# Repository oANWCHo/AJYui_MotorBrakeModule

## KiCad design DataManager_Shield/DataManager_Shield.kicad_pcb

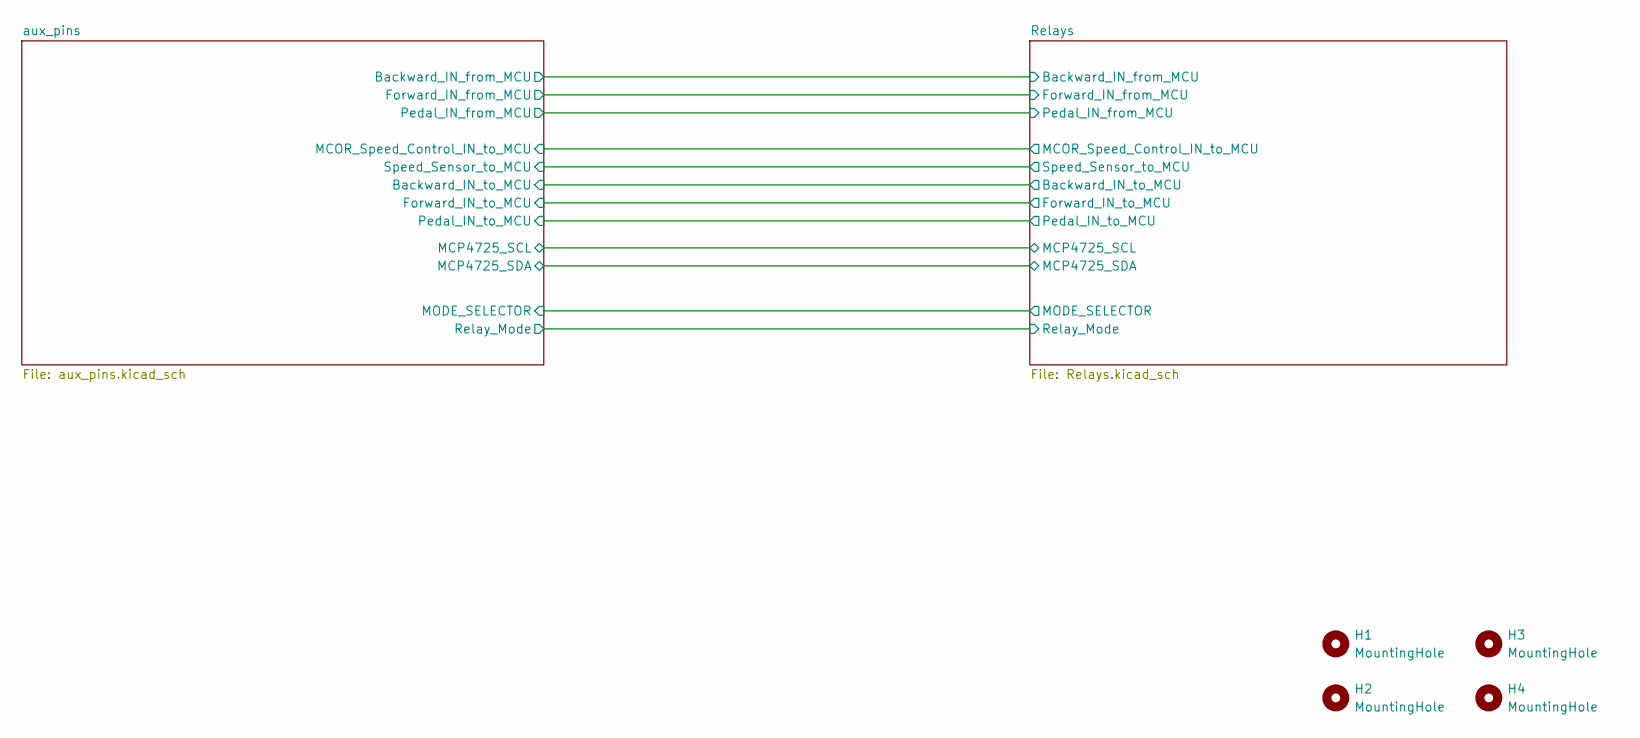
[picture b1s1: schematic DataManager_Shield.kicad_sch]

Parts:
H1, H2, H3, H4: MountingHole; MountingHole_3.2mm_M3_DIN965_Pad

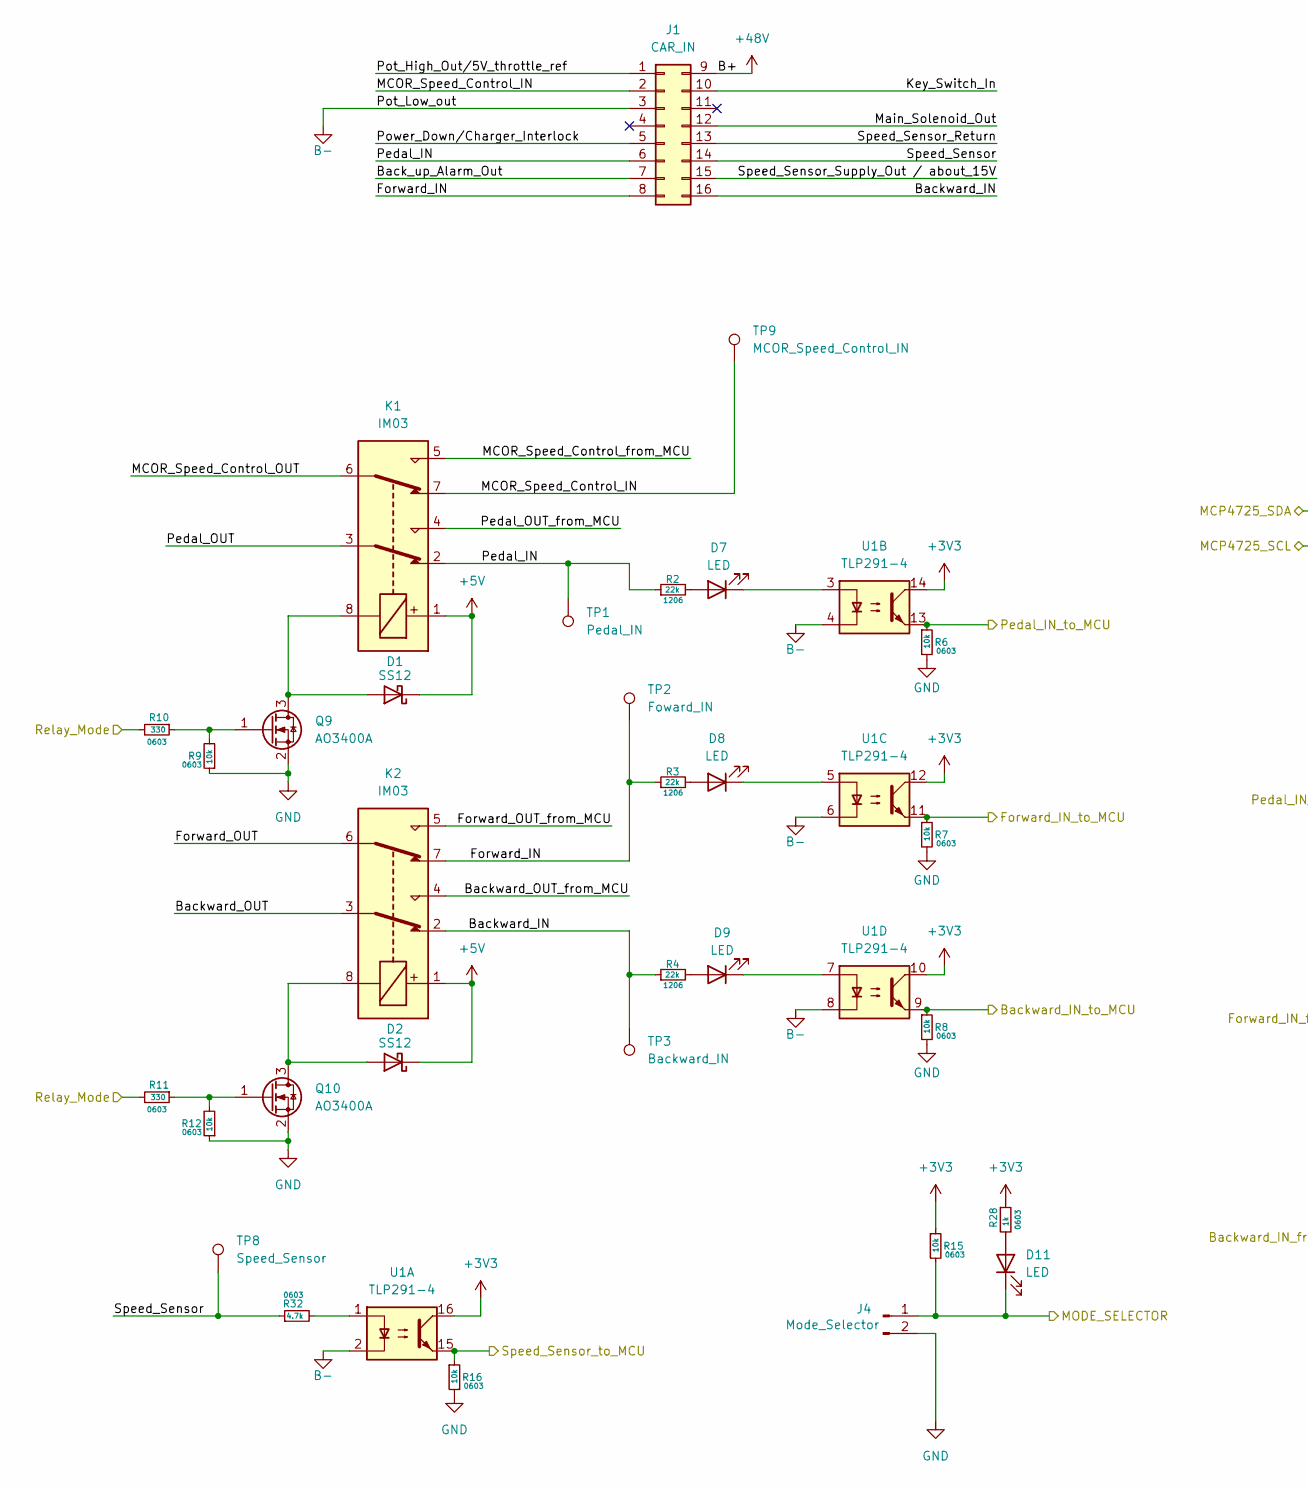
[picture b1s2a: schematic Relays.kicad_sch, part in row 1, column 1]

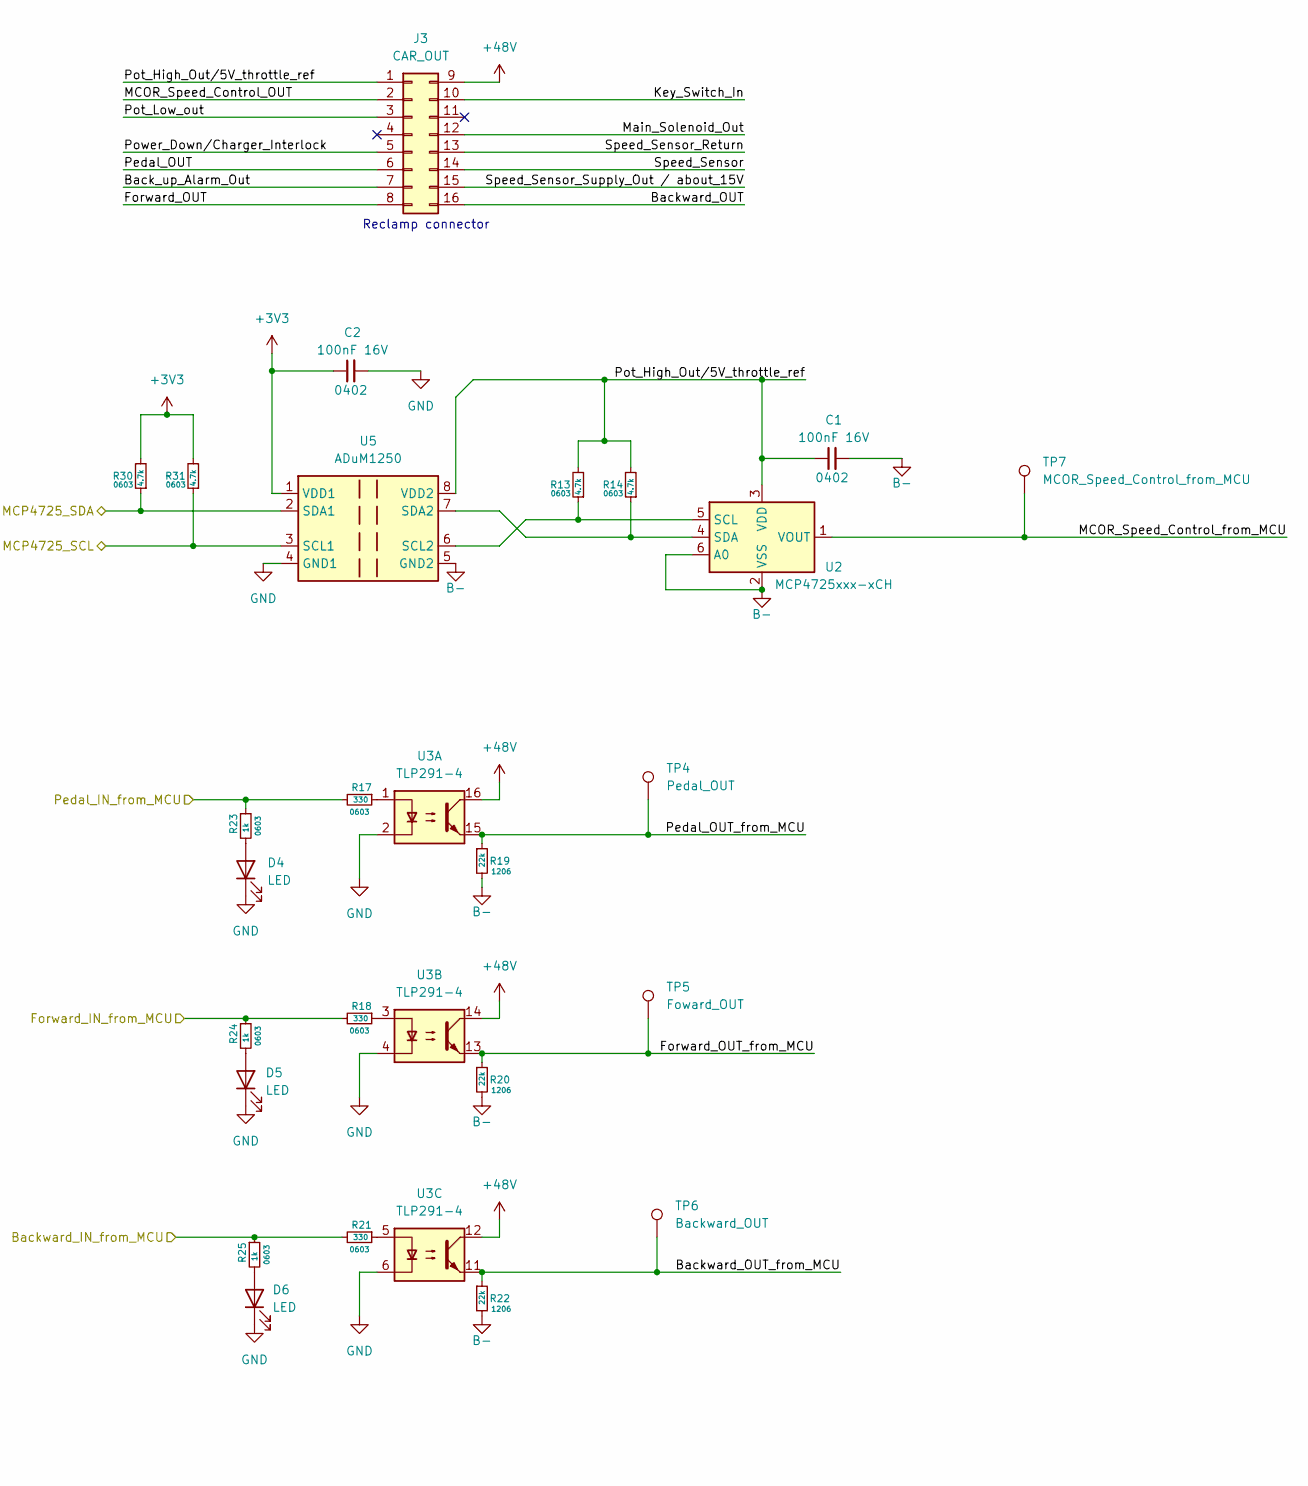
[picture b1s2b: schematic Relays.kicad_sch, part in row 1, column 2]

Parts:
C1, C2: 100nF 16V; C_0402_1005Metric; JLCPCB Part # C1525
D1, D2: SS12; D_SMA; JLCPCB Part # C18199177
D4, D5, D6, D7, D8, D9, D11: LED; LED_0603_1608Metric; JLCPCB Part # C2287
J1: CAR_IN; Molex_Mini-Fit_Jr_5569-16A2_2x08_P4.20mm_Horizontal; JLCPCB Part # C485577
J3: CAR_OUT; Molex_Mini-Fit_Jr_5569-16A2_2x08_P4.20mm_Horizontal; JLCPCB Part # C485577
J4: Mode_Selector; JST_XH_S2B-XH-A_1x02_P2.50mm_Horizontal; JLCPCB Part # C163035
K1, K2: IM03; Relay_2P2T_10x6mm_TE_IMxxG; JLCPCB Part # C2153100
Q9, Q10: AO3400A; SOT-23; JLCPCB Part # C20917
R2, R3, R4, R19, R20, R22: 22k; R_1206_3216Metric; JLCPCB Part # C25654
R6, R7, R8, R9, R12, R15, R16: 10k; R_0603_1608Metric; JLCPCB Part # C130232
R10, R11, R17, R18, R21: 330; R_0603_1608Metric; JLCPCB Part # C23138
R13, R14, R30, R31, R32: 4.7k; R_0603_1608Metric; JLCPCB Part # C23162
R23, R24, R25, R28: 1k; R_0603_1608Metric; JLCPCB Part # C21190
TP1: Pedal_IN; TestPoint_Pad_1.0x1.0mm
TP2: Foward_IN; TestPoint_Pad_1.0x1.0mm
TP3: Backward_IN; TestPoint_Pad_1.0x1.0mm
TP4: Pedal_OUT; TestPoint_Pad_1.0x1.0mm
TP5: Foward_OUT; TestPoint_Pad_1.0x1.0mm
TP6: Backward_OUT; TestPoint_Pad_1.0x1.0mm
TP7: MCOR_Speed_Control_from_MCU; TestPoint_Pad_1.0x1.0mm
TP8: Speed_Sensor; TestPoint_Pad_1.0x1.0mm
TP9: MCOR_Speed_Control_IN; TestPoint_Pad_1.0x1.0mm
U1, U3: TLP291-4; SOP-16_4.4x10.4mm_P1.27mm; JLCPCB Part # C60900
U2: MCP4725xxx-xCH; SOT-23-6; JLCPCB Part # C144198
U5: ADuM1250; SOIC-8_3.9x4.9mm_P1.27mm; JLCPCB Part # C13839

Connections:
+3V3: C2.1, R15.1, R28.1, R30.2, R31.2, U1.10, U1.12, U1.14, U1.16, U5.1 (VDD1); also elsewhere on the board
+5V: D1.1 (K), D2.1 (K), K1.1, K2.1; also elsewhere on the board
+48V: J1.9, J3.9, U3.12, U3.14, U3.16
/Relays/ Speed_Sensor_Supply_Out / about_15V: J1.15, J3.15
/Relays/Back_up_Alarm_Out: J1.7, J3.7
/Relays/Backward_IN: J1.16, K2.2, R4.1, TP3.1 (1_1)
/Relays/Backward_OUT: J3.16, K2.3
/Relays/Backward_OUT_from_MCU: K2.4, R22.1, TP6.1 (1_1), U3.11
/Relays/Forward_IN: J1.8, K2.7, R3.1, TP2.1 (1_1)
/Relays/Forward_OUT: J3.8, K2.6
/Relays/Forward_OUT_from_MCU: K2.5, R20.1, TP5.1 (1_1), U3.13
/Relays/Key_Switch_In: J1.10, J3.10
/Relays/MCOR_Speed_Control_IN: J1.2, K1.7, TP9.1 (1_1)
/Relays/MCOR_Speed_Control_OUT: J3.2, K1.6
/Relays/MCOR_Speed_Control_from_MCU: K1.5, TP7.1 (1_1), U2.1 (VOUT)
/Relays/Main_Solenoid_Out: J1.12, J3.12
/Relays/Pedal_IN: J1.6, K1.2, R2.1, TP1.1 (1_1)
/Relays/Pedal_OUT: J3.6, K1.3
/Relays/Pedal_OUT_from_MCU: K1.4, R19.1, TP4.1 (1_1), U3.15
/Relays/Pot_High_Out/5V_throttle_ref: C1.1, J1.1, J3.1, R13.2, R14.2, U2.3 (VDD), U5.8 (VDD2)
/Relays/Power_Down/Charger_Interlock: J1.5, J3.5
/Relays/Speed_Sensor: J1.14, J3.14, R32.1, TP8.1 (1_1)
/Relays/Speed_Sensor_Return: J1.13, J3.13
/aux_pins/PA8: R30.1, U5.2 (SDA1); also elsewhere on the board
/aux_pins/PA9: R31.1, U5.3 (SCL1); also elsewhere on the board
/aux_pins/PA10: R10.2, R11.2; also elsewhere on the board
/aux_pins/PA15: R16.1, U1.15; also elsewhere on the board
/aux_pins/PB0: R6.1, U1.13; also elsewhere on the board
/aux_pins/PC4: R8.1, U1.9; also elsewhere on the board
/aux_pins/PC5: R7.1, U1.11; also elsewhere on the board
/aux_pins/PC6: R18.2, R24.1; also elsewhere on the board
/aux_pins/PC7: R17.2, R23.1; also elsewhere on the board
/aux_pins/PC8: R21.2, R25.1; also elsewhere on the board
/aux_pins/PC9: D11.1 (K), J4.1, R15.2; also elsewhere on the board
B-: C1.2, J1.3, J3.3, R19.2, R20.2, R22.2, U1.2, U1.4, U1.6, U1.8, U2.2 (VSS), U2.6 (A0), U5.5 (GND2)
GND: C2.2, D4.1 (K), D5.1 (K), D6.1 (K), J4.2, Q9.2 (S), Q10.2 (S), R6.2, R7.2, R8.2, R9.1, R12.1, R16.2, U3.2, U3.4, U3.6, U5.4 (GND1); also elsewhere on the board
unnamed: D1.2 (A), K1.8, Q9.3 (D)
unnamed: D2.2 (A), K2.8, Q10.3 (D)
unnamed: D4.2 (A), R23.2
unnamed: D5.2 (A), R24.2
unnamed: D6.2 (A), R25.2
unnamed: D7.2 (A), R2.2
unnamed: D7.1 (K), U1.3
unnamed: D8.2 (A), R3.2
unnamed: D8.1 (K), U1.5
unnamed: D9.2 (A), R4.2
unnamed: D9.1 (K), U1.7
unnamed: D11.2 (A), R28.2
unnamed: Q9.1 (G), R9.2, R10.1
unnamed: Q10.1 (G), R11.1, R12.2
unnamed: R17.1, U3.1
unnamed: R18.1, U3.3
unnamed: R21.1, U3.5
unnamed: R32.2, U1.1
unnamed: R13.1, U2.5 (SCL), U5.6 (SCL2)
unnamed: R14.1, U2.4 (SDA), U5.7 (SDA2)

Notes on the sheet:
Reclamp connector

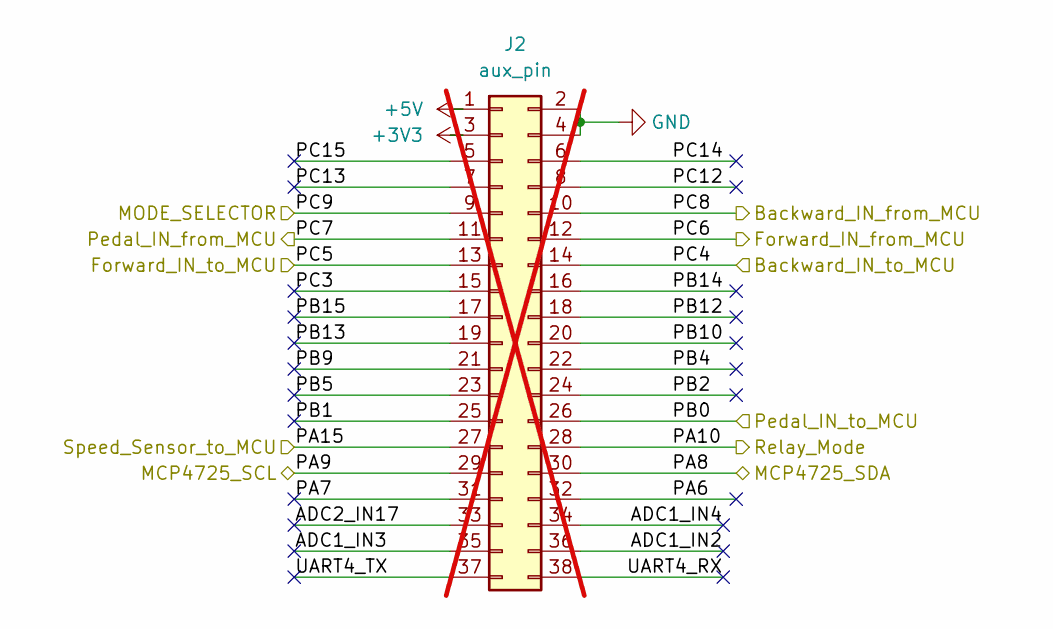
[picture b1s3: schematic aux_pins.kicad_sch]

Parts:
J2: aux_pin; PinSocket_2x19_P2.54mm_Vertical; JLCPCB Part # C2883962; not fitted

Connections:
+3V3: J2.3; also elsewhere on the board
+5V: J2.1; also elsewhere on the board
/aux_pins/ADC1_IN2: J2.36
/aux_pins/ADC1_IN3: J2.35
/aux_pins/ADC1_IN4: J2.34
/aux_pins/ADC2_IN17: J2.33
/aux_pins/PA6: J2.32
/aux_pins/PA7: J2.31
/aux_pins/PA8: J2.30; also elsewhere on the board
/aux_pins/PA9: J2.29; also elsewhere on the board
/aux_pins/PA10: J2.28; also elsewhere on the board
/aux_pins/PA15: J2.27; also elsewhere on the board
/aux_pins/PB0: J2.26; also elsewhere on the board
/aux_pins/PB1: J2.25
/aux_pins/PB2: J2.24
/aux_pins/PB4: J2.22
/aux_pins/PB5: J2.23
/aux_pins/PB9: J2.21
/aux_pins/PB10: J2.20
/aux_pins/PB12: J2.18
/aux_pins/PB13: J2.19
/aux_pins/PB14: J2.16
/aux_pins/PB15: J2.17
/aux_pins/PC3: J2.15
/aux_pins/PC4: J2.14; also elsewhere on the board
/aux_pins/PC5: J2.13; also elsewhere on the board
/aux_pins/PC6: J2.12; also elsewhere on the board
/aux_pins/PC7: J2.11; also elsewhere on the board
/aux_pins/PC8: J2.10; also elsewhere on the board
/aux_pins/PC9: J2.9; also elsewhere on the board
/aux_pins/PC12: J2.8
/aux_pins/PC13: J2.7
/aux_pins/PC14: J2.6
/aux_pins/PC15: J2.5
/aux_pins/UART4_RX: J2.38
/aux_pins/UART4_TX: J2.37
GND: J2.2, J2.4; also elsewhere on the board

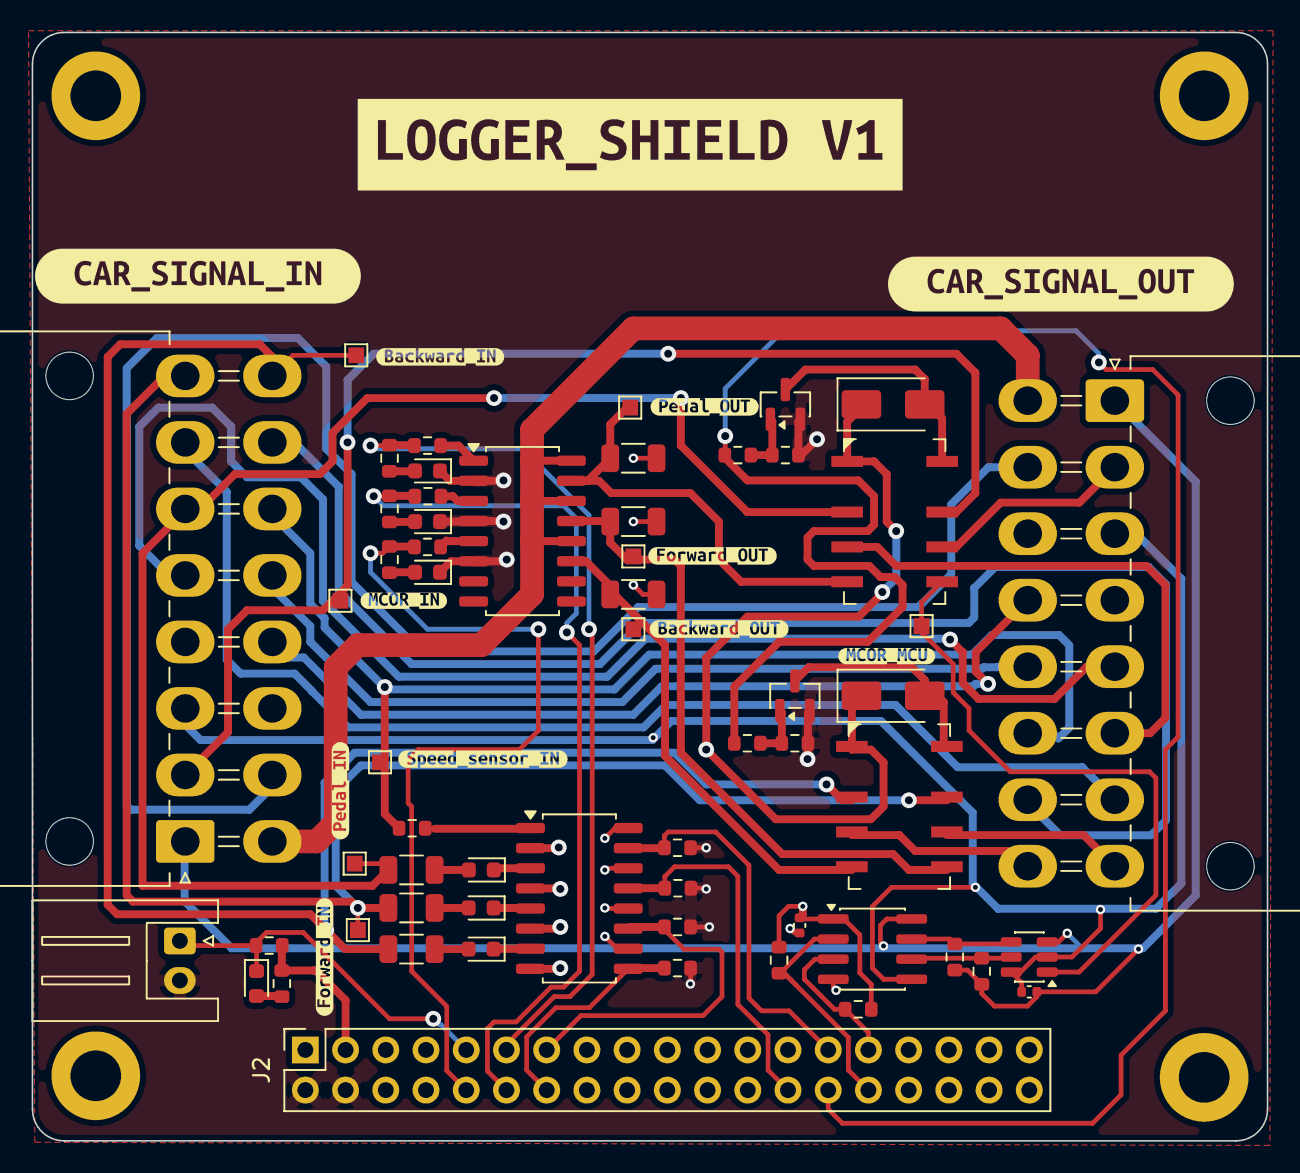
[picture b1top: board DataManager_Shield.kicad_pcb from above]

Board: 4 copper layers, 78.0 x 70.0 mm, 75 parts (0 on the bottom side), 56 nets.

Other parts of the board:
kibuzzard-6A36AE6B: G***; kibuzzard-6A36AE6B
kibuzzard-6A36AE7E: G***; kibuzzard-6A36AE7E
kibuzzard-6A36B0C2: G***; kibuzzard-6A36B0C2
kibuzzard-6A36B0D5: G***; kibuzzard-6A36B0D5
kibuzzard-6A36B2C1: G***; kibuzzard-6A36B2C1
kibuzzard-6A36B03F: G***; kibuzzard-6A36B03F
kibuzzard-6A36B04E: G***; kibuzzard-6A36B04E
kibuzzard-6A36B06A: G***; kibuzzard-6A36B06A
kibuzzard-6A36B07D: G***; kibuzzard-6A36B07D
kibuzzard-6A36B090: G***; kibuzzard-6A36B090
kibuzzard-6A36CCD0: G***; kibuzzard-6A36CCD0
kibuzzard-6AB2994C: G***; kibuzzard-6AB2994C

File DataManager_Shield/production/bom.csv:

Designator,Footprint,Quantity,Value,LCSC Part #
"C1, C2",0402,2,100nF 16V,C1525
"D1, D2",D_SMA,2,SS12,C18199177
"D11, D4, D5, D6, D7, D8, D9",0603,7,LED,C2287
J1,Molex_Mini-Fit_Jr_5569-16A2_2x08_P4.20mm_Horizontal,1,CAR_IN,C485577
J3,Molex_Mini-Fit_Jr_5569-16A2_2x08_P4.20mm_Horizontal,1,CAR_OUT,C485577
J4,JST_XH_S2B-XH-A_1x02_P2.50mm_Horizontal,1,Mode_Selector,C163035
"K1, K2",Relay_2P2T_10x6mm_TE_IMxxG,2,IM03,C2153100
"Q10, Q9",SOT-23,2,AO3400A,C20917
"R10, R11, R17, R18, R21",0603,5,330,C23138
"R12, R15, R16, R6, R7, R8, R9",0603,7,10k,C130232
"R13, R14, R30, R31, R32",0603,5,4.7k,C23162
"R19, R2, R20, R22, R3, R4",1206,6,22k,C25654
"R23, R24, R25, R28",0603,4,1k,C21190
TP1,TestPoint_Pad_1.0x1.0mm,1,Pedal_IN,
TP2,TestPoint_Pad_1.0x1.0mm,1,Foward_IN,
TP3,TestPoint_Pad_1.0x1.0mm,1,Backward_IN,
TP4,TestPoint_Pad_1.0x1.0mm,1,Pedal_OUT,
TP5,TestPoint_Pad_1.0x1.0mm,1,Foward_OUT,
TP6,TestPoint_Pad_1.0x1.0mm,1,Backward_OUT,
TP7,TestPoint_Pad_1.0x1.0mm,1,MCOR_Speed_Control_from_MCU,
TP8,TestPoint_Pad_1.0x1.0mm,1,Speed_Sensor,
TP9,TestPoint_Pad_1.0x1.0mm,1,MCOR_Speed_Control_IN,
"U1, U3",SOP-16_4.4x10.4mm_P1.27mm,2,TLP291-4,C60900
U2,SOT-23-6,1,MCP4725xxx-xCH,C144198
U5,SOIC-8_3.9x4.9mm_P1.27mm,1,ADuM1250,C13839

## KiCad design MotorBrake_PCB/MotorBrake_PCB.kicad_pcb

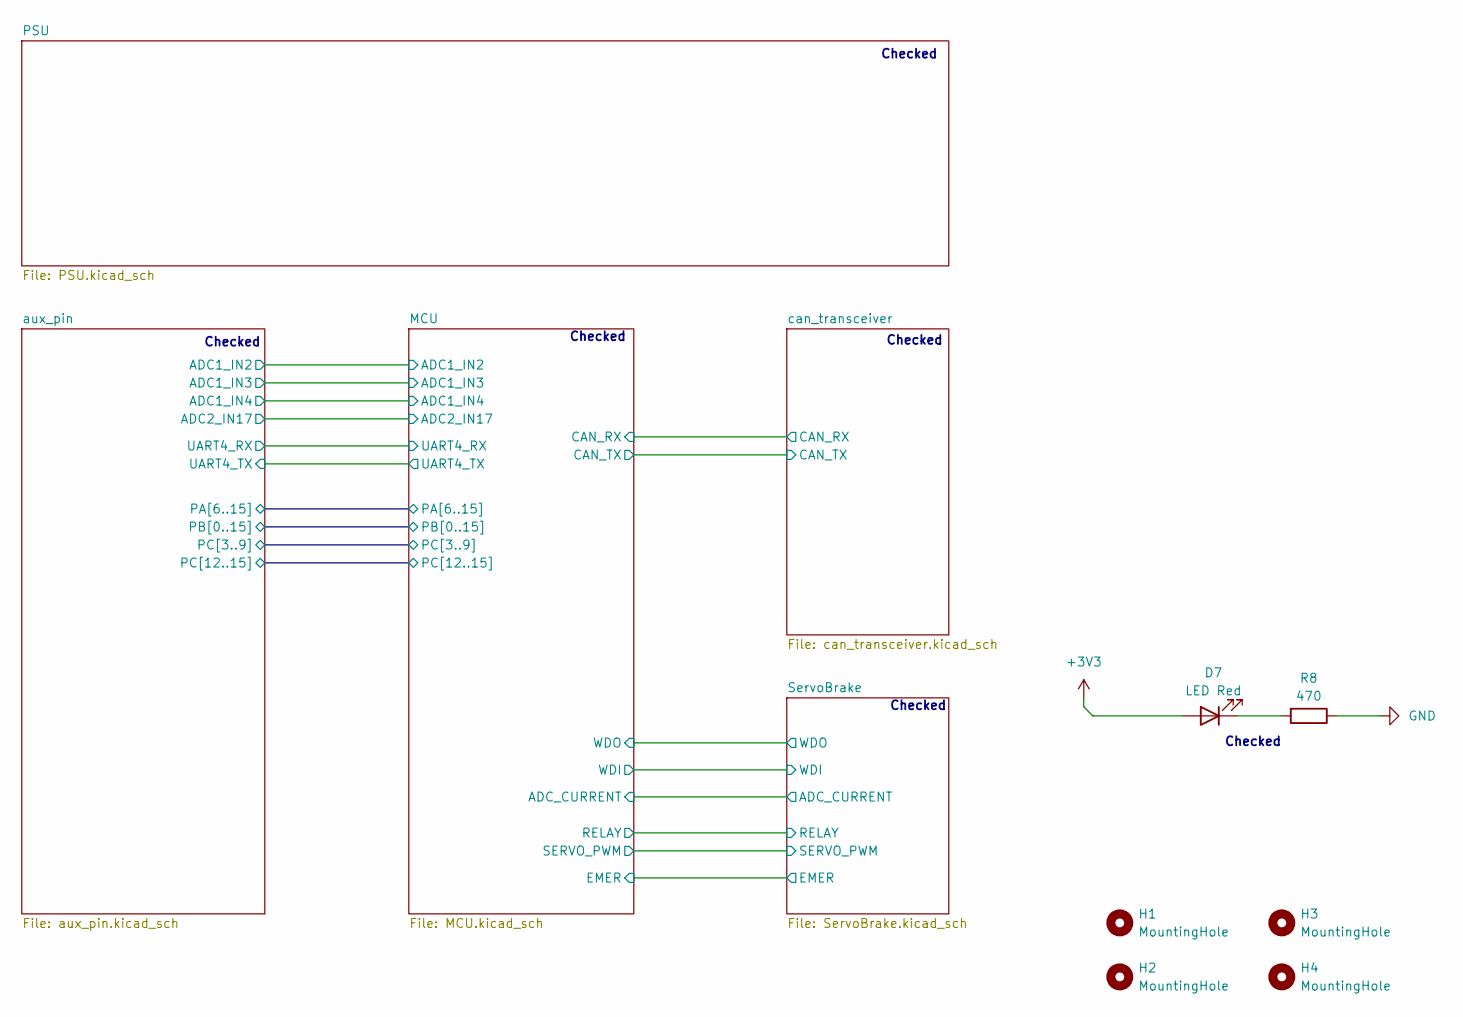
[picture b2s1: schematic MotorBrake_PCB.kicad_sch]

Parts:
D7: LED Red; LED_0603_1608Metric; JLCPCB Part # C2286
H1, H2, H3, H4: MountingHole; MountingHole_3.2mm_M3_DIN965_Pad
R8: 470; R_0603_1608Metric; JLCPCB Part # C23179

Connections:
+3V3: D7.2 (A); also elsewhere on the board
GND: R8.1; also elsewhere on the board
unnamed: D7.1 (K), R8.2

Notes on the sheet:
Checked

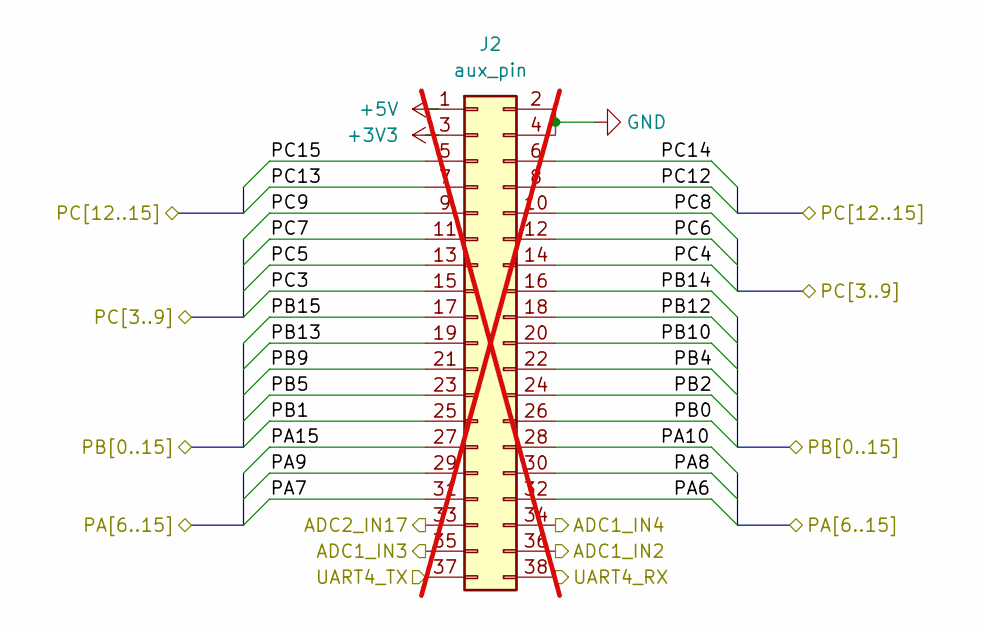
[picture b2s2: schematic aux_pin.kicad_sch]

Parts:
J2: aux_pin; PinSocket_2x19_P2.54mm_Vertical; JLCPCB Part # C2883962; not fitted

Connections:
+3V3: J2.3; also elsewhere on the board
+5V: J2.1; also elsewhere on the board
/MCU/ADC1_IN2: J2.36; also elsewhere on the board
/MCU/ADC1_IN3: J2.35; also elsewhere on the board
/MCU/ADC1_IN4: J2.34; also elsewhere on the board
/MCU/ADC2_IN17: J2.33; also elsewhere on the board
/MCU/PA6: J2.32; also elsewhere on the board
/MCU/PA7: J2.31; also elsewhere on the board
/MCU/PA8: J2.30; also elsewhere on the board
/MCU/PA9: J2.29; also elsewhere on the board
/MCU/PA10: J2.28; also elsewhere on the board
/MCU/PA15: J2.27; also elsewhere on the board
/MCU/PB0: J2.26; also elsewhere on the board
/MCU/PB1: J2.25; also elsewhere on the board
/MCU/PB2: J2.24; also elsewhere on the board
/MCU/PB4: J2.22; also elsewhere on the board
/MCU/PB5: J2.23; also elsewhere on the board
/MCU/PB9: J2.21; also elsewhere on the board
/MCU/PB10: J2.20; also elsewhere on the board
/MCU/PB12: J2.18; also elsewhere on the board
/MCU/PB13: J2.19; also elsewhere on the board
/MCU/PB14: J2.16; also elsewhere on the board
/MCU/PB15: J2.17; also elsewhere on the board
/MCU/PC3: J2.15; also elsewhere on the board
/MCU/PC4: J2.14; also elsewhere on the board
/MCU/PC5: J2.13; also elsewhere on the board
/MCU/PC6: J2.12; also elsewhere on the board
/MCU/PC7: J2.11; also elsewhere on the board
/MCU/PC8: J2.10; also elsewhere on the board
/MCU/PC9: J2.9; also elsewhere on the board
/MCU/PC12: J2.8; also elsewhere on the board
/MCU/PC13: J2.7; also elsewhere on the board
/MCU/PC14: J2.6; also elsewhere on the board
/MCU/PC15: J2.5; also elsewhere on the board
/MCU/UART4_RX: J2.38; also elsewhere on the board
/MCU/UART4_TX: J2.37; also elsewhere on the board
GND: J2.2, J2.4; also elsewhere on the board

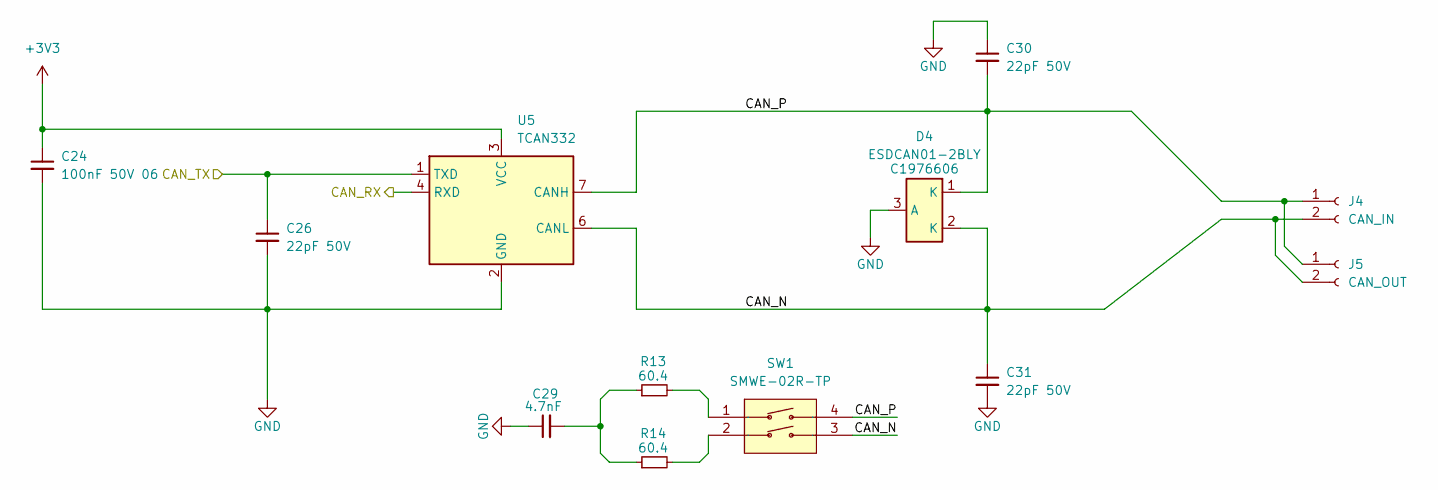
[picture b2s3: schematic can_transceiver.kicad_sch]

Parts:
C24: 100nF 50V 06; C_0603_1608Metric; LCSC Part # C1525
C26, C30, C31: 22pF 50V; C_0402_1005Metric; LCSC Part # C70464
C29: 4.7nF; C_0402_1005Metric; LCSC Part # C70464
D4: ESDCAN01-2BLY; TSOT-23; JLCPCB Part # C1976606
J4: CAN_IN; JST_XH_B2B-XH-AM_1x02_P2.50mm_Vertical; JLCPCB Part # C158012
J5: CAN_OUT; JST_XH_B2B-XH-AM_1x02_P2.50mm_Vertical; JLCPCB Part # C158012
R13, R14: 60.4; R_0603_1608Metric; LCSC Part # C23090
SW1: SMWE-02R-TP; SW-TH_SMWE-02R-TP; Manufacturer Part SMWE-02R-TP; LCSC Part Name 1位拨码开关
U5: TCAN332; SOIC-8_3.9x4.9mm_P1.27mm; JLCPCB Part # C73651

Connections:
+3V3: C24.1, U5.3 (VCC); also elsewhere on the board
/MCU/CAN_RX: U5.4 (RXD); also elsewhere on the board
/MCU/CAN_TX: C26.1, U5.1 (TXD); also elsewhere on the board
/can_transceiver/CAN_N: C31.1, D4.2 (K), J4.2, J5.2, SW1.3, U5.6 (CANL)
/can_transceiver/CAN_P: C30.2, D4.1 (K), J4.1, J5.1, SW1.4, U5.7 (CANH)
GND: C24.2, C26.2, C29.1, C30.1, C31.2, D4.3 (A), U5.2 (GND); also elsewhere on the board
unnamed: C29.2, R13.1, R14.1
unnamed: R13.2, SW1.1
unnamed: R14.2, SW1.2

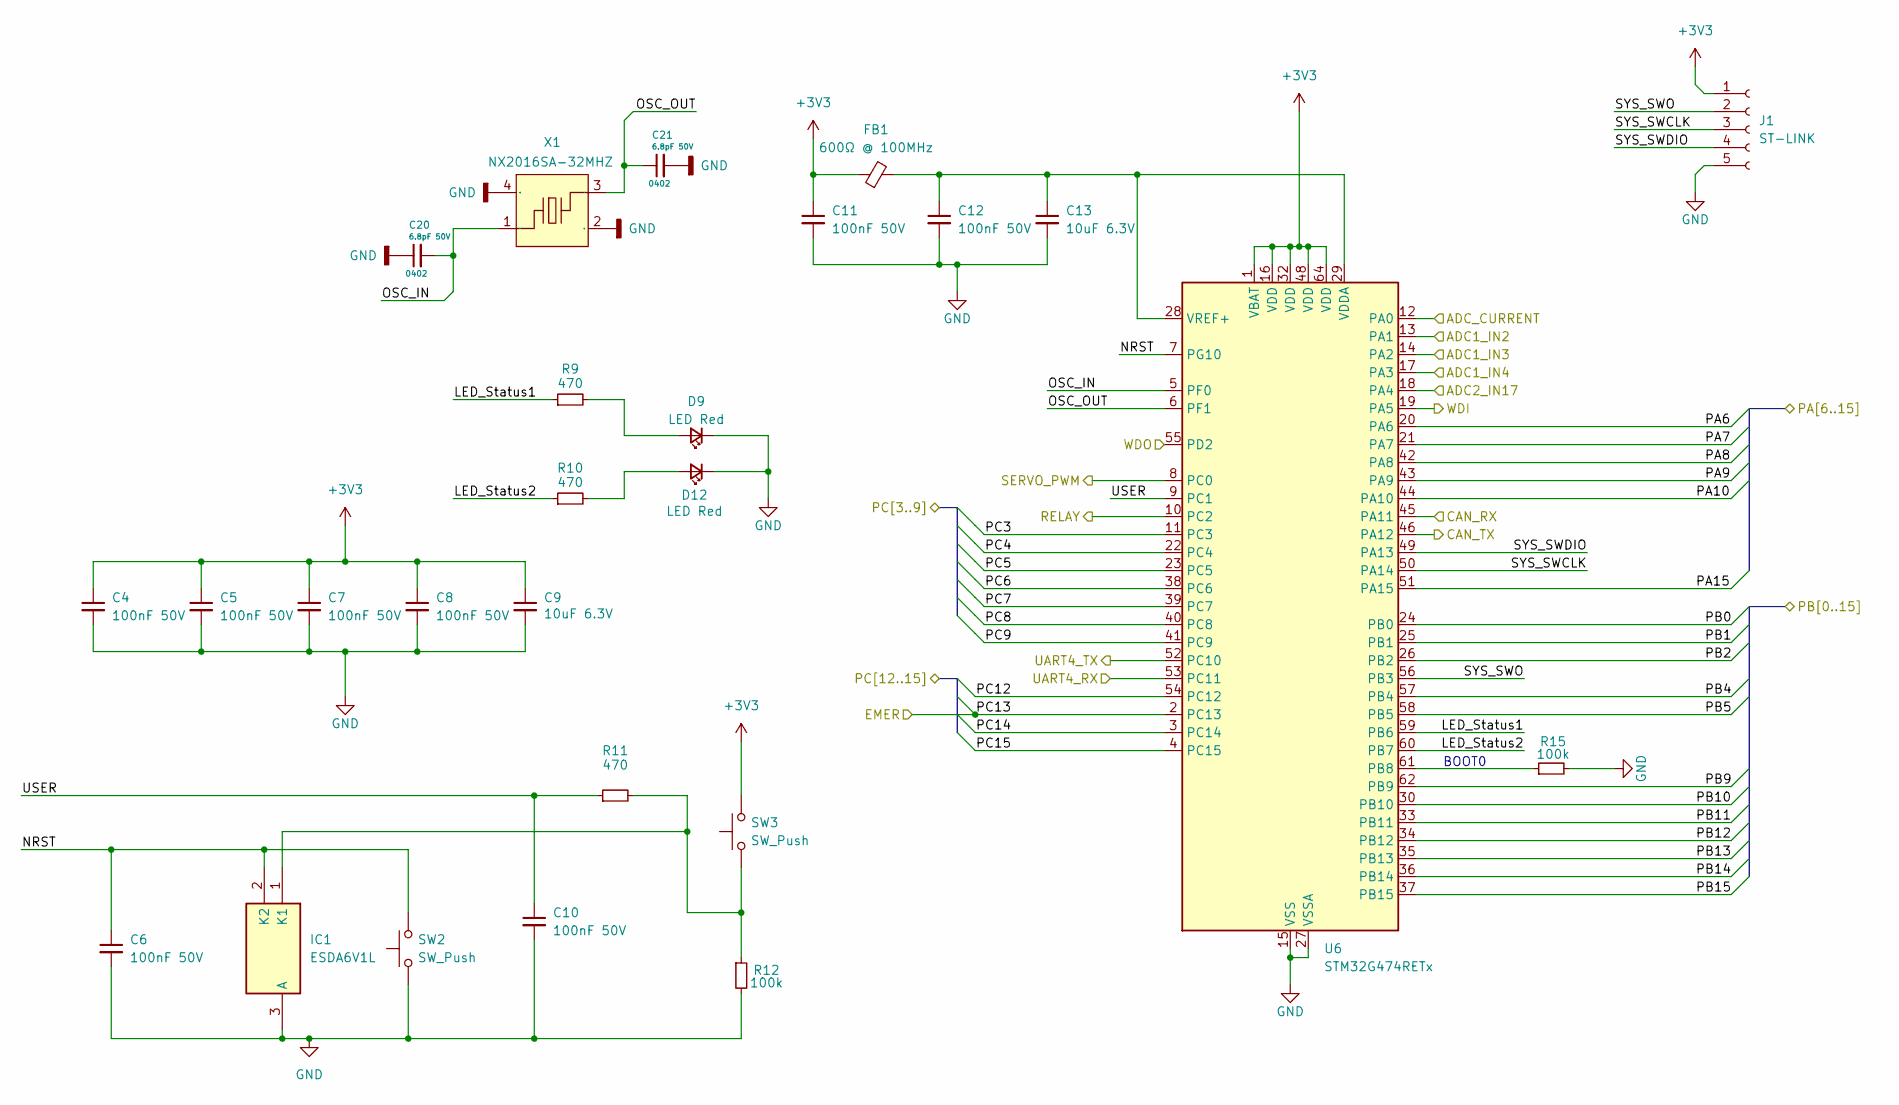
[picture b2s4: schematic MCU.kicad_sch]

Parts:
C4, C5, C6, C7, C8, C10, C11, C12: 100nF 50V; C_0402_1005Metric; LCSC Part # C1525
C9, C13: 10uF 6.3V; C_0402_1005Metric; LCSC Part # C15525
C20, C21: 6.8pF 50V; C_0402_1005Metric; JLC C5448819
D9, D12: LED Red; LED_0603_1608Metric; LCSC Part # C2290
FB1: 600Ω @ 100MHz; L_0402_1005Metric; JLCPCB Part # C14182
IC1: ESDA6V1L; SOT105P242X150-3N; Mouser Part Number 511-ESDA6V1L
J1: ST-LINK; PinSocket_1x05_P2.54mm_Vertical; JLCPCB Part # C2932699
R9, R10, R11: 470; R_0603_1608Metric; LCSC Part # C25104
R12, R15: 100k; R_0402_1005Metric; LCSC Part # C25741
SW2, SW3: SW_Push; SW_Tactile_SPST_NO_Straight_CK_PTS636Sx25SMTRLFS; LCSC Part # C318938
U6: STM32G474RETx; LQFP-64_10x10mm_P0.5mm; JLCPCB Part # C521608
X1: NX2016SA-32MHZ; CRYSTAL-SMD_4P-L2.0-W1.6-BL; Manufacturer Part NX2016SA-32MHZ-STD-CZS-5; LCSC Part Name NX2016SA 32MHz 8pF ±10ppm

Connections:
+3V3: C4.1, C5.1, C7.1, C8.1, C9.1, C11.1, FB1.1, J1.1, SW3.2, U6.1 (VBAT), U6.16 (VDD), U6.32 (VDD), U6.48 (VDD), U6.64 (VDD); also elsewhere on the board
/MCU/ADC1_IN2: U6.13 (PA1); also elsewhere on the board
/MCU/ADC1_IN3: U6.14 (PA2); also elsewhere on the board
/MCU/ADC1_IN4: U6.17 (PA3); also elsewhere on the board
/MCU/ADC2_IN17: U6.18 (PA4); also elsewhere on the board
/MCU/ADC_CURRENT: U6.12 (PA0); also elsewhere on the board
/MCU/CAN_RX: U6.45 (PA11); also elsewhere on the board
/MCU/CAN_TX: U6.46 (PA12); also elsewhere on the board
/MCU/LED_Status1: R9.1, U6.59 (PB6)
/MCU/LED_Status2: R10.1, U6.60 (PB7)
/MCU/NRST: C6.1, IC1.2 (K2), SW2.2, U6.7 (PG10)
/MCU/OSC_IN: C20.2, U6.5 (PF0), X1.1
/MCU/OSC_OUT: C21.1, U6.6 (PF1), X1.3
/MCU/PA6: U6.20 (PA6); also elsewhere on the board
/MCU/PA7: U6.21 (PA7); also elsewhere on the board
/MCU/PA8: U6.42 (PA8); also elsewhere on the board
/MCU/PA9: U6.43 (PA9); also elsewhere on the board
/MCU/PA10: U6.44 (PA10); also elsewhere on the board
/MCU/PA15: U6.51 (PA15); also elsewhere on the board
/MCU/PB0: U6.24 (PB0); also elsewhere on the board
/MCU/PB1: U6.25 (PB1); also elsewhere on the board
/MCU/PB2: U6.26 (PB2); also elsewhere on the board
/MCU/PB4: U6.57 (PB4); also elsewhere on the board
/MCU/PB5: U6.58 (PB5); also elsewhere on the board
/MCU/PB9: U6.62 (PB9); also elsewhere on the board
/MCU/PB10: U6.30 (PB10); also elsewhere on the board
/MCU/PB11: U6.33 (PB11)
/MCU/PB12: U6.34 (PB12); also elsewhere on the board
/MCU/PB13: U6.35 (PB13); also elsewhere on the board
/MCU/PB14: U6.36 (PB14); also elsewhere on the board
/MCU/PB15: U6.37 (PB15); also elsewhere on the board
/MCU/PC3: U6.11 (PC3); also elsewhere on the board
/MCU/PC4: U6.22 (PC4); also elsewhere on the board
/MCU/PC5: U6.23 (PC5); also elsewhere on the board
/MCU/PC6: U6.38 (PC6); also elsewhere on the board
/MCU/PC7: U6.39 (PC7); also elsewhere on the board
/MCU/PC8: U6.40 (PC8); also elsewhere on the board
/MCU/PC9: U6.41 (PC9); also elsewhere on the board
/MCU/PC12: U6.54 (PC12); also elsewhere on the board
/MCU/PC13: U6.2 (PC13); also elsewhere on the board
/MCU/PC14: U6.3 (PC14); also elsewhere on the board
/MCU/PC15: U6.4 (PC15); also elsewhere on the board
/MCU/RELAY: U6.10 (PC2); also elsewhere on the board
/MCU/SERVO_PWM: U6.8 (PC0); also elsewhere on the board
/MCU/SYS_SWCLK: J1.3, U6.50 (PA14)
/MCU/SYS_SWDIO: J1.4, U6.49 (PA13)
/MCU/SYS_SWO: J1.2, U6.56 (PB3)
/MCU/UART4_RX: U6.53 (PC11); also elsewhere on the board
/MCU/UART4_TX: U6.52 (PC10); also elsewhere on the board
/MCU/USER: C10.1, R11.1, U6.9 (PC1)
/MCU/WDI: U6.19 (PA5); also elsewhere on the board
/MCU/WDO: U6.55 (PD2); also elsewhere on the board
GND: C4.2, C5.2, C6.2, C7.2, C8.2, C9.2, C10.2, C11.2, C12.2, C13.2, C20.1, C21.2, D9.1 (K), D12.1 (K), IC1.3 (A), J1.5, R12.2, R15.2, SW2.1, U6.15 (VSS), U6.27 (VSSA), U6.31 (VSS), U6.47 (VSS), U6.63 (VSS), X1.2 (GND), X1.4 (GND); also elsewhere on the board
unnamed: D9.2 (A), R9.2
unnamed: D12.2 (A), R10.2
unnamed: IC1.1 (K1), R11.2, R12.1, SW3.1
unnamed: R15.1, U6.61 (PB8)
unnamed: C12.1, C13.1, FB1.2, U6.28 (VREF+), U6.29 (VDDA)

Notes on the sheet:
BOOT0
